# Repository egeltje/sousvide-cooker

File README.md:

sousvide-cooker
===============

AVR atmega32 code for controlling a sous vide cooker. See http://www.ewak.net/blog/sous-vide-cooker/

NOTE: This code is no longer updated, since I got an Anova sous-vide cooker. This satisfies my needs for a cooker and I am no longer building my own.

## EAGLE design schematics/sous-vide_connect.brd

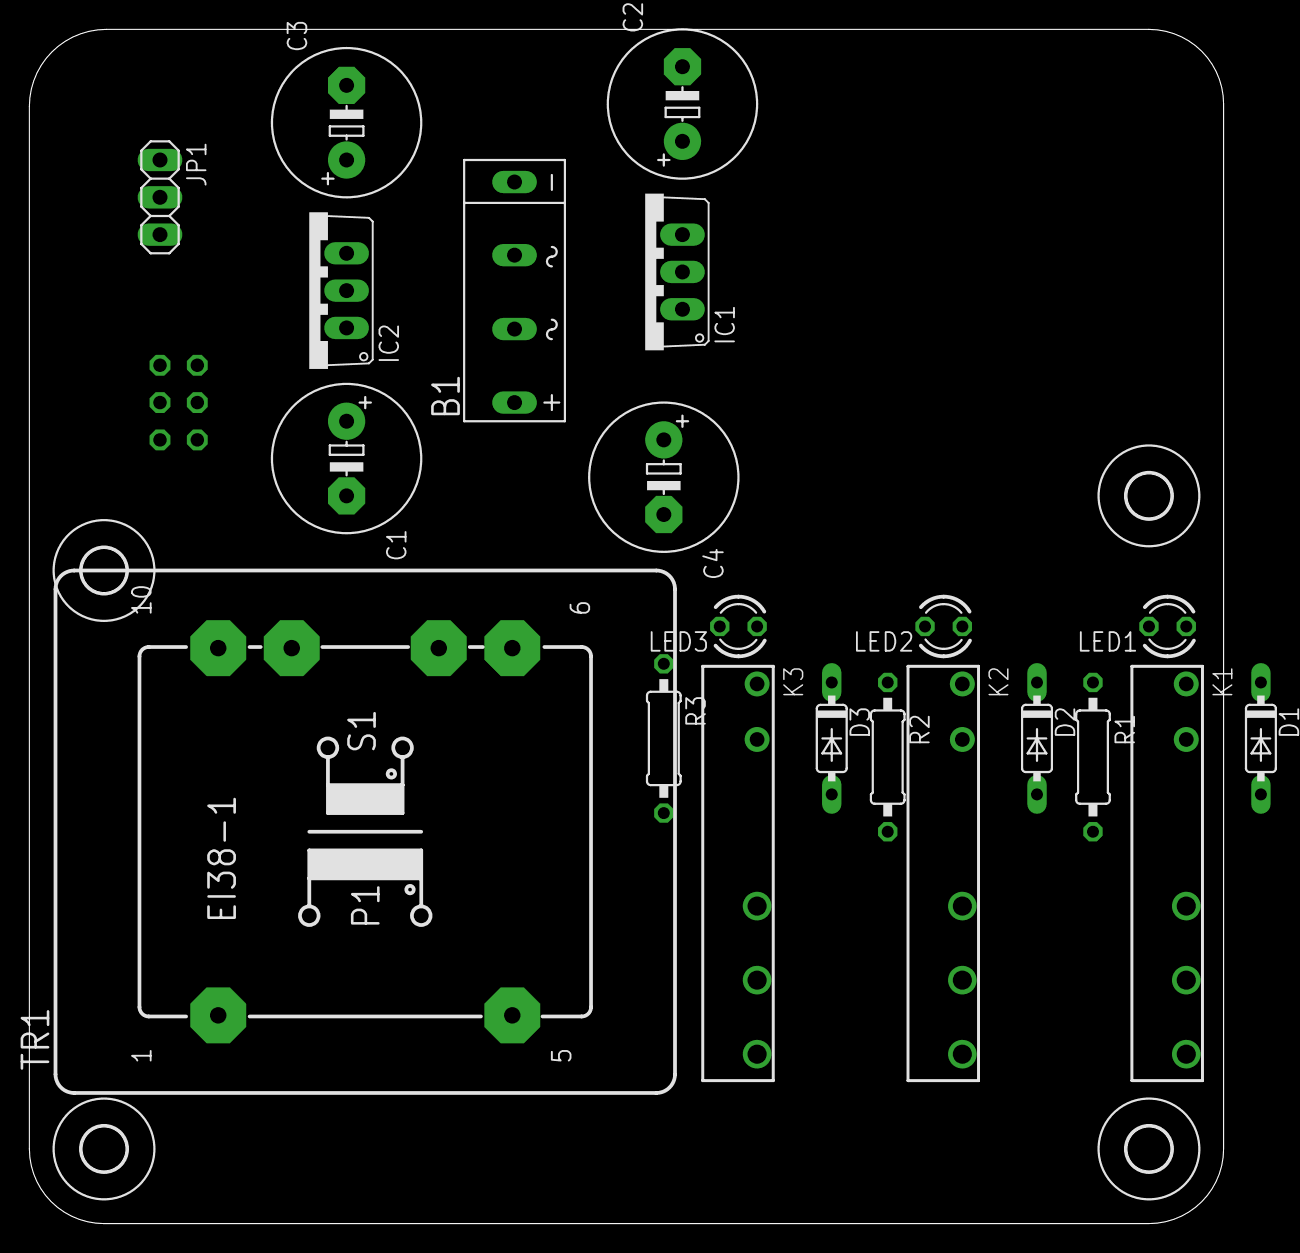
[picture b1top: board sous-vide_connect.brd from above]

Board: 2 copper layers, 81.3 x 81.3 mm, 26 parts (1 on the bottom side), 13 nets, no tracks yet.

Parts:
B1: 2KBB-R
C1, C2, C3, C4: E5-10,5
D1, D2, D3: 1N4148DO35-7; DO35-7
H1, H2, H3, H4: MOUNT-HOLE3.0; 3,0
IC1, IC2: 7805TV; TO220V
JP1: 1X03
K1, K2, K3: APF30212C
LED1, LED2, LED3: LED3MM
R1, R2, R3: 0207/10
SV1: ML6
TR1: EI38-1

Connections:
GND: B1.-, C1.-, C2.-, C3.-, C4.-, D1.A, D2.A, D3.A, IC1.2, IC2.2, JP1.3, K1.2, K2.2, K3.2, R1.2, R2.2, R3.2, SV1.6
unnamed: B1.AC1, TR1.9
unnamed: B1.AC2, TR1.7
unnamed: D1.C, K1.1, LED1.A, SV1.1
unnamed: B1.+, C1.+, C4.+, IC1.1, IC2.1
unnamed: JP1.2, SV1.4
unnamed: LED1.K, R1.1
unnamed: LED2.K, R2.1
unnamed: D2.C, K2.1, LED2.A, SV1.3
unnamed: D3.C, K3.1, LED3.A, SV1.5
unnamed: LED3.K, R3.1
unnamed: C2.+, IC1.3
VCC: C3.+, IC2.3, JP1.1, SV1.2

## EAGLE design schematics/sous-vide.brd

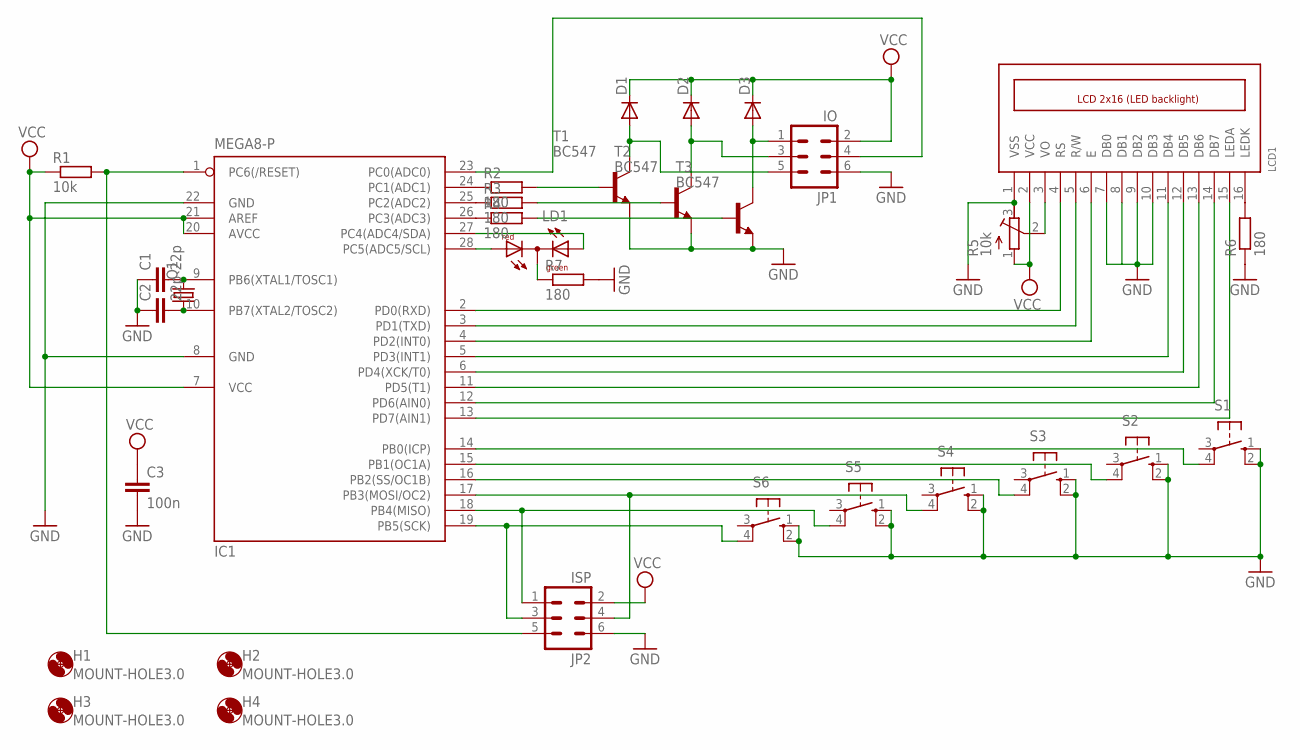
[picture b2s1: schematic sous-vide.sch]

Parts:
C1, C2: 22p; C025-025X050
C3: 100n; C025-025X050
D1, D2, D3: DIODE-D-2.5; D-2.5
H1, H2, H3, H4: MOUNT-HOLE3.0; 3,0
IC1: MEGA8-P; DIL28-3
JP1: IO; ML6
JP2: ISP; ML6
LCD1: LCD_2X16_SIL; HY-1602F
LD1: DUOLED-RG-C; DUOLED-C-5MM
Q1: CRYSTALHC49U-V; HC49U-V
R1: 10k; 0207/7
R2, R3, R4: 180; 0207/2V
R5: 10k; RTRIM3339P
R6, R7: 180; 0207/7
S1, S2, S3, S4, S5, S6: 40-XX; B3F-40XX
T1, T2, T3: BC547; TO92

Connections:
GND: C1.1, C2.1, C3.2, IC1.8 (GND), IC1.22 (GND), JP1.6, JP2.6, LCD1.1 (VSS), LCD1.7 (DB0), LCD1.8 (DB1), LCD1.9 (DB2), LCD1.10 (DB3), R5.3 (A), R6.1, R7.2, S1.1 (S), S1.2 (S1), S2.1 (S), S2.2 (S1), S3.1 (S), S3.2 (S1), S4.1 (S), S4.2 (S1), S5.1 (S), S5.2 (S1), S6.1 (S), S6.2 (S1), T1.1 (E), T2.1 (E), T3.1 (E)
unnamed: C1.2, IC1.9 (PB6(XTAL1/TOSC1)), Q1.2
unnamed: LCD1.16 (LEDK), R6.2
unnamed: IC1.23 (PC0(ADC0)), JP1.4
unnamed: IC1.24 (PC1(ADC1)), R2.1
unnamed: IC1.25 (PC2(ADC2)), R3.1
unnamed: IC1.26 (PC3(ADC3)), R4.1
unnamed: LD1.C, R7.1
unnamed: IC1.28 (PC5(ADC5/SCL)), LD1.AR
unnamed: IC1.27 (PC4(ADC4/SDA)), LD1.AX (AG)
unnamed: R2.2, T1.2 (B)
unnamed: R3.2, T2.2 (B)
unnamed: R4.2, T3.2 (B)
unnamed: D1.A, JP1.5, T1.3 (C)
unnamed: LCD1.3 (VO), R5.2 (S)
unnamed: C2.2, IC1.10 (PB7(XTAL2/TOSC2)), Q1.1
unnamed: D2.A, JP1.3, T2.3 (C)
unnamed: D3.A, JP1.1, T3.3 (C)
unnamed: IC1.19 (PB5(SCK)), JP2.3, S6.4 (P1)
unnamed: IC1.18 (PB4(MISO)), JP2.1, S5.4 (P1)
unnamed: IC1.2 (PD0(RXD)), LCD1.4 (RS)
unnamed: IC1.3 (PD1(TXD)), LCD1.5 (R/W)
unnamed: IC1.4 (PD2(INT0)), LCD1.6 (E)
unnamed: IC1.17 (PB3(MOSI/OC2)), JP2.4, S4.4 (P1)
unnamed: IC1.5 (PD3(INT1)), LCD1.11 (DB4)
unnamed: IC1.6 (PD4(XCK/T0)), LCD1.12 (DB5)
unnamed: IC1.1 (PC6(/RESET)), JP2.5, R1.2
unnamed: IC1.11 (PD5(T1)), LCD1.13 (DB6)
unnamed: IC1.12 (PD6(AIN0)), LCD1.14 (DB7)
unnamed: IC1.13 (PD7(AIN1)), LCD1.15 (LEDA)
unnamed: IC1.16 (PB2(SS/OC1B)), S3.4 (P1)
unnamed: IC1.14 (PB0(ICP)), S1.4 (P1)
unnamed: IC1.15 (PB1(OC1A)), S2.4 (P1)
VCC: C3.1, D1.C, D2.C, D3.C, IC1.7 (VCC), IC1.20 (AVCC), IC1.21 (AREF), JP1.2, JP2.2, LCD1.2 (VCC), R1.1, R5.1 (E)

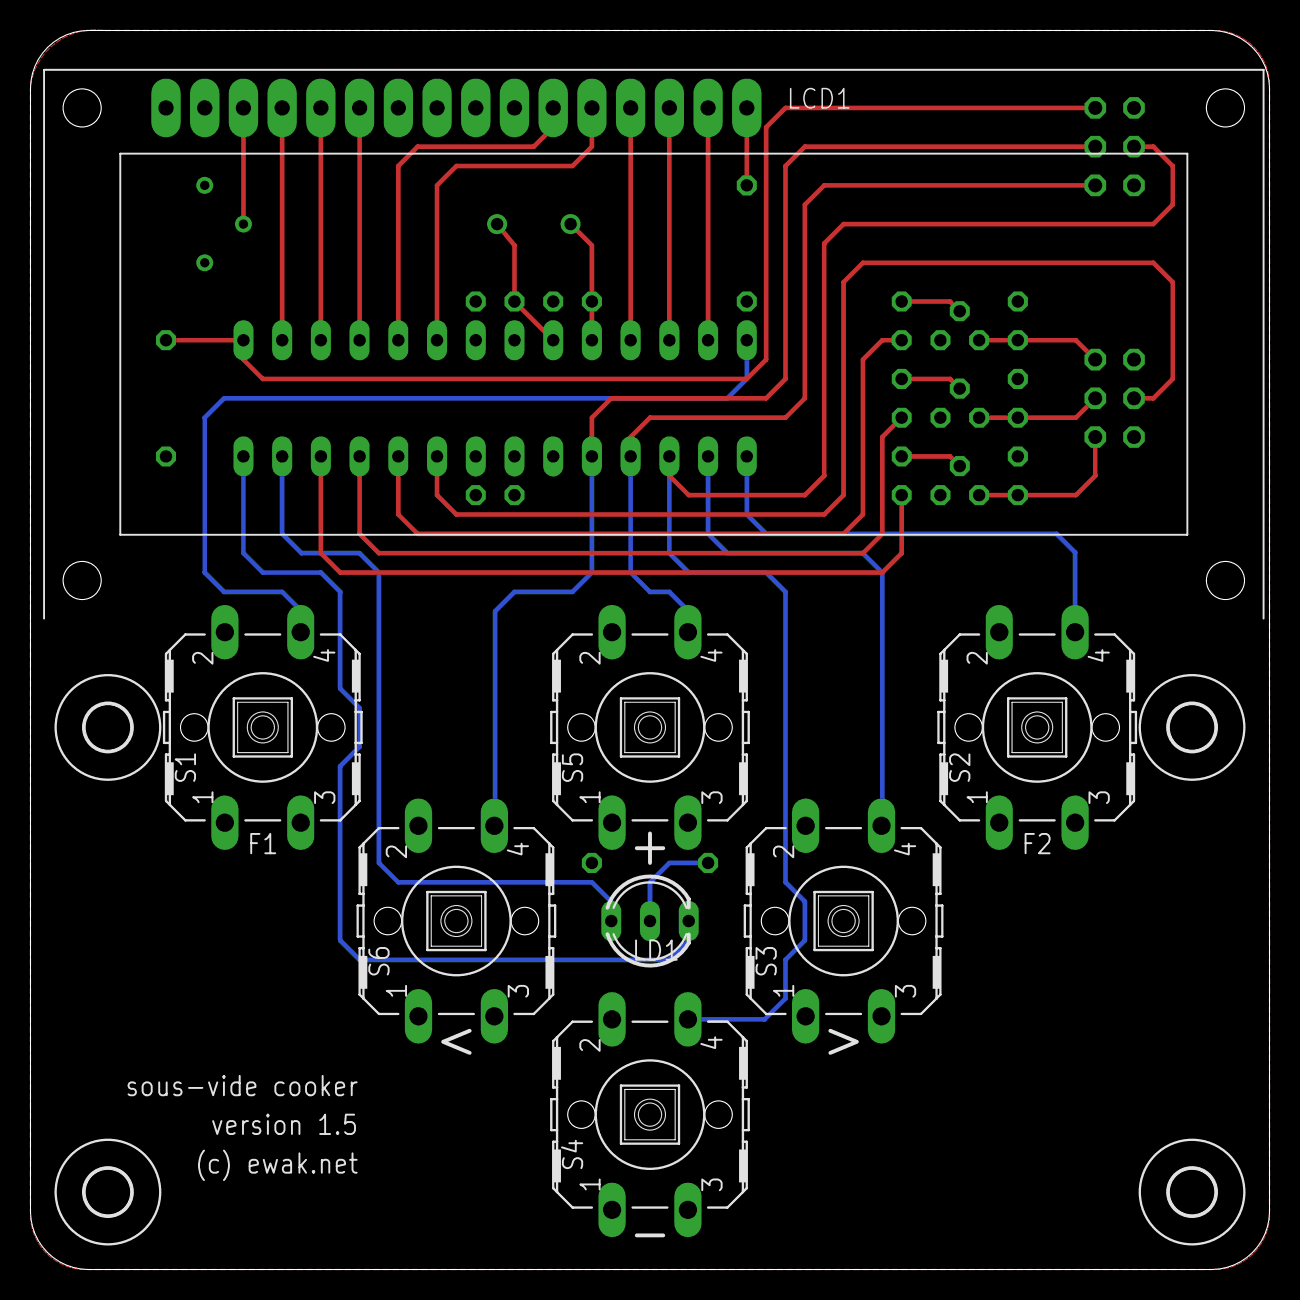
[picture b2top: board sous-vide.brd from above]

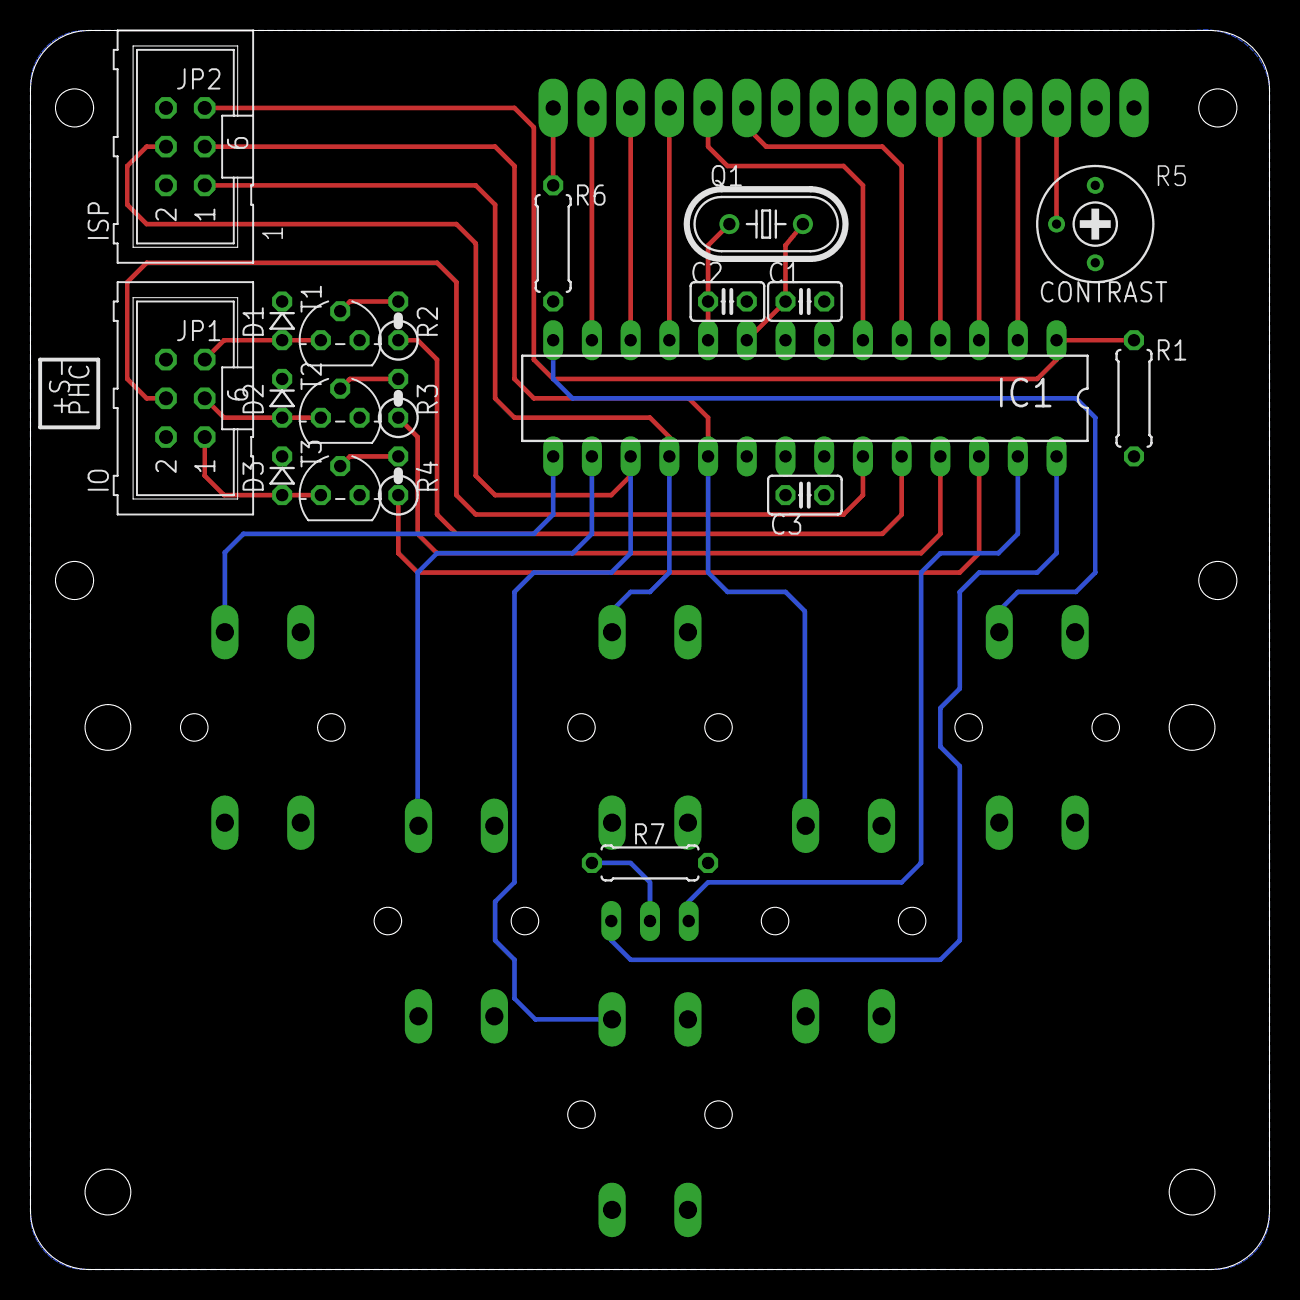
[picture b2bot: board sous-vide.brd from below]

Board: 2 copper layers, 81.3 x 81.3 mm, 32 parts (20 on the bottom side), 34 nets.

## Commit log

2013-08-14 updated documentation in code
2013-12-29 Electronic schema and board updated
    Created an 8x8 cm board for cpu, display and buttons.
2014-01-01 Added 3d designs for plug
    Added 3d designs for the plug holding the heater, pump and sensor.
2014-01-03 Added 3d designs for display
    First design for case. Plug will be connected to the bottom. Needs
    compartiment for mains voltage stuff.
2014-01-17 Bug fixes and display change
    Erroneous comment-start removed, Pump and Heater place on display
    swapped.
2014-04-02 Optimized PCB
    Optimized PCB with easier traces for buttons.
2014-04-27 initial steps to move from at32u4 naar at32
2014-04-27 Working ATmega32 code. JTAG disabled with fuses.
2014-04-27 Working ATmega32 code. JTAG disabled with fuses. Display on PORTC
2014-04-28 Average temp reading + ISP connector
    Temp readings are averaged per second before comparing to the set
    temperature. Added ISP header to board for on-board reprogramming.
2014-04-28 Declared variable
    Forgot to declare variable used for averaging temperature readings.
2014-04-29 Added general HALT function and moved defines to .h file.
2014-04-30 Moved from _BV(1) to direct 0x01 bit patterns.
2014-04-30 Added halting easter egg.
2014-05-01 Removed easter egg.
2014-05-01 Harmonized HALT function
2014-05-01 Fixed bug that allowed time reset while timer was running.
2014-05-01 Updated schematic and PCB
    Now includes 4th led for reading indicator. Moved ISP connector to more
    accessible location.
2014-06-05 Switched to ATmega328 and updated schematics and board.
2014-06-05 Moved R6 on board for symmetry with R1.
2014-06-06 Changed connectors and renumbered parts on schematic and board.
2014-06-06 Minor shift in components.
2014-08-12 minor tweaks in component placement, sent to pcb manufacturer
2015-03-30 Reworked schema and pcb for new buttons and display.
2015-03-30 Minor tweaks before shipping to pcb manufacturer.
2015-04-16 Fixed VCC/VDD/VSS/GND issue with display, renumbered parts, updated port assignment in code.
2015-04-18 Fixed backlighting.
2015-04-22 Removed eagle.epf file from repository.
2015-04-22 Display rewrite.
2015-05-05 compiling but completely not functioning code.
2015-05-05 Migrated to Eclipse as IDE, split functions per file, reduced number of global variables.
2015-05-05 Reordered interrupt events, _iTime is still running too fast.
2015-05-05 Fixed timer issue by placing _iTime++ inside TICK handler.
2015-05-06 Moved global iStatus to local _iStatus.
2015-05-06 Moved array to struct.
2015-05-06 Main functions working correctly, next steps are config functions.
2015-05-07 Main program finished, display updates streamlined.
2015-05-07 Continued working on menu structure for configuration.
2015-05-07 Converted menu to char pointer.
2015-05-08 Menu function with dynamic strings working. Screen not yet updating correctly.
2015-05-08 Continued on submenus.
2015-05-08 Submenus working by initializing _iButtonOld with the current iButton value when initializing.
2015-05-08 Cleaned up submenus.
2015-05-08 Removed two temp variables from fConfigPeriodEdit function.
2015-05-08 Steamlined calibration functions.
2015-05-08 Added variable to show the set temperature in fConfigCalibrationMeasurement.
2015-05-12 Optimized struct memory allocation using malloc().
2015-05-13 Moved pointers to stPeriods and stCalibration to global variables. Edits to periods are working now.
2015-05-15 Solved wrongly updating period (always period 0) by storing the period in a temp variable and using that. Horrible...
2015-05-15 Menus fully functional.
2015-05-15 Added temperature calibration and additional confirmation dialog for factory reset.
2015-05-15 Fixed small bug in calculating calibrated temperature reading.
2015-05-15 Moved temperature calibration to main loop in stead of interrupt routine.
2015-05-16 Fixed EEPROM reading offset error.
2015-05-16 Moved generid display functions to dedicated dispaly.c file.
2015-05-17 Moved display layout to specific functions for more flexibility and uniformity.
2015-05-17 Move to dedicated display functions complete. Last remaining issue is calculating (and using) T(t) for even temperature change over set time.
2015-05-19 Continued working on Temp calculations.
2015-05-19 Completed temperature calculation.
2015-05-20 Removed button and LED and added crystal for more precise timing over longer periods.
2015-05-21 PCB button and connector layout rearranged. NOT COMPATIBEL WITH PRE-1.5 CODE.
2015-05-21 Mapped button definition in code to v1.5 of the pcb.
2015-05-22 Optimized traces and button definitions and send to pcb production as version 1.5
2015-05-28 Started working on connect pcb for transformer and relays.
2019-09-18 Uodated readme
    Added abandon-notice for this repository.
